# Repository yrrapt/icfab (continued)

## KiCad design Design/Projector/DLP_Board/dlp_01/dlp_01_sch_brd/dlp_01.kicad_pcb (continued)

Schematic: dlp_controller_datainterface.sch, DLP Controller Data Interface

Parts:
R48, R49, R50, R51: 7.87k; R_0603_1608Metric; part-num CRCW06037K87FKEA
U1, U2: DLPC3437; BGA-225_15x15_13.1x13.1mm; part-num DLPC3437CZEZ

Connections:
/application_connectors/DATEN_A: U2.P2 (DATAEN_CMD); also elsewhere on the board
/application_connectors/DATEN_B: U1.P2 (DATAEN_CMD); also elsewhere on the board
/application_connectors/HSYNC_A: U2.N5 (HSYNC_CS); also elsewhere on the board
/application_connectors/HSYNC_B: U1.N5 (HSYNC_CS); also elsewhere on the board
/application_connectors/IO_B34_LN4: U1.R9 (PDATA_22); also elsewhere on the board
/application_connectors/IO_B34_LN6: U1.R8 (PDATA_20); also elsewhere on the board
/application_connectors/IO_B34_LN8: U1.R7 (PDATA_18); also elsewhere on the board
/application_connectors/IO_B34_LN11: U1.R6 (PDATA_16); also elsewhere on the board
/application_connectors/IO_B34_LP4: U1.P10 (PDATA_23); also elsewhere on the board
/application_connectors/IO_B34_LP6: U1.P9 (PDATA_21); also elsewhere on the board
/application_connectors/IO_B34_LP8: U1.P8 (PDATA_19); also elsewhere on the board
/application_connectors/IO_B34_LP11: U1.P7 (PDATA_17); also elsewhere on the board
/application_connectors/IO_B35_LN2: U2.R9 (PDATA_22); also elsewhere on the board
/application_connectors/IO_B35_LN4: U2.R8 (PDATA_20); also elsewhere on the board
/application_connectors/IO_B35_LN6: U2.R7 (PDATA_18); also elsewhere on the board
/application_connectors/IO_B35_LN8: U2.R6 (PDATA_16); also elsewhere on the board
/application_connectors/IO_B35_LN10: U2.R5 (PDATA_14); also elsewhere on the board
/application_connectors/IO_B35_LN14: U2.R4 (PDATA_12); also elsewhere on the board
/application_connectors/IO_B35_LN16: U2.R3 (PDATA_10); also elsewhere on the board
/application_connectors/IO_B35_LN18: U2.R1 (PDATA_8); also elsewhere on the board
/application_connectors/IO_B35_LN20: U2.N2 (PDATA_6); also elsewhere on the board
/application_connectors/IO_B35_LN22: U2.M2 (PDATA_4); also elsewhere on the board
/application_connectors/IO_B35_LN23: U2.K1 (PDATA_1); also elsewhere on the board
/application_connectors/IO_B35_LN24: U2.L2 (PDATA_2); also elsewhere on the board
/application_connectors/IO_B35_LP2: U2.P10 (PDATA_23); also elsewhere on the board
/application_connectors/IO_B35_LP4: U2.P9 (PDATA_21); also elsewhere on the board
/application_connectors/IO_B35_LP6: U2.P8 (PDATA_19); also elsewhere on the board
/application_connectors/IO_B35_LP8: U2.P7 (PDATA_17); also elsewhere on the board
/application_connectors/IO_B35_LP10: U2.P6 (PDATA_15); also elsewhere on the board
/application_connectors/IO_B35_LP14: U2.P5 (PDATA_13); also elsewhere on the board
/application_connectors/IO_B35_LP16: U2.P4 (PDATA_11); also elsewhere on the board
/application_connectors/IO_B35_LP18: U2.R2 (PDATA_9); also elsewhere on the board
/application_connectors/IO_B35_LP20: U2.N1 (PDATA_7); also elsewhere on the board
/application_connectors/IO_B35_LP22: U2.M1 (PDATA_5); also elsewhere on the board
/application_connectors/IO_B35_LP23: U2.K2 (PDATA_0); also elsewhere on the board
/application_connectors/IO_B35_LP24: U2.L1 (PDATA_3); also elsewhere on the board
/application_connectors/LCD_DATA0: U1.K2 (PDATA_0); also elsewhere on the board
/application_connectors/LCD_DATA1: U1.K1 (PDATA_1); also elsewhere on the board
/application_connectors/LCD_DATA2: U1.L2 (PDATA_2); also elsewhere on the board
/application_connectors/LCD_DATA3: U1.L1 (PDATA_3); also elsewhere on the board
/application_connectors/LCD_DATA4: U1.M2 (PDATA_4); also elsewhere on the board
/application_connectors/LCD_DATA5: U1.M1 (PDATA_5); also elsewhere on the board
/application_connectors/LCD_DATA6: U1.N2 (PDATA_6); also elsewhere on the board
/application_connectors/LCD_DATA7: U1.N1 (PDATA_7); also elsewhere on the board
/application_connectors/LCD_DATA8: U1.R1 (PDATA_8); also elsewhere on the board
/application_connectors/LCD_DATA9: U1.R2 (PDATA_9); also elsewhere on the board
/application_connectors/LCD_DATA10: U1.R3 (PDATA_10); also elsewhere on the board
/application_connectors/LCD_DATA11: U1.P4 (PDATA_11); also elsewhere on the board
/application_connectors/LCD_DATA12: U1.R4 (PDATA_12); also elsewhere on the board
/application_connectors/LCD_DATA13: U1.P5 (PDATA_13); also elsewhere on the board
/application_connectors/LCD_DATA14: U1.R5 (PDATA_14); also elsewhere on the board
/application_connectors/LCD_DATA15: U1.P6 (PDATA_15); also elsewhere on the board
/application_connectors/PCLK_A: U2.P3 (PCLK); also elsewhere on the board
/application_connectors/PCLK_B: U1.P3 (PCLK); also elsewhere on the board
/application_connectors/PDM_CVS_TE_A: R51.2, U2.N4 (PDM_CVS_TE); also elsewhere on the board
/application_connectors/PDM_CVS_TE_B: R49.2, U1.N4 (PDM_CVS_TE); also elsewhere on the board
/application_connectors/VSYNC_A: U2.P1 (VSYNC_WE); also elsewhere on the board
/application_connectors/VSYNC_B: U1.P1 (VSYNC_WE); also elsewhere on the board
GND: R48.2, R49.1, R50.2, R51.1; also elsewhere on the board
unnamed: R48.1, U1.N6 (3DR)
unnamed: R50.1, U2.N6 (3DR)

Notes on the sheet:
Slave
Master

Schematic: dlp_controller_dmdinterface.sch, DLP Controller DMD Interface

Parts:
R52, R53: 43R; R_0603_1608Metric; part-num CRCW060343R0FKEA
U1, U2: DLPC3437; BGA-225_15x15_13.1x13.1mm; part-num DLPC3437CZEZ

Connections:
/dlp_controller/DMD_DEN_ARSTZ: U1.B1 (DMD_DEN_ARSTZ); also elsewhere on the board
/dlp_controller/DMD_LS_CLK: R52.2; also elsewhere on the board
/dlp_controller/DMD_LS_RDATA: U1.B2 (DMD_LS_RDATA); also elsewhere on the board
/dlp_controller/DMD_LS_WDATA: R53.2; also elsewhere on the board
/dlp_controller/mDMD_HS_CLK_N: U1.B7 (DMD_HS_CLK_N); also elsewhere on the board
/dlp_controller/mDMD_HS_CLK_P: U1.A7 (DMD_HS_CLK_P); also elsewhere on the board
/dlp_controller/mDMD_HS_WDATAA_N: U1.B11 (DMD_HS_WDATA_A_N); also elsewhere on the board
/dlp_controller/mDMD_HS_WDATAA_P: U1.A11 (DMD_HS_WDATA_A_P); also elsewhere on the board
/dlp_controller/mDMD_HS_WDATAB_N: U1.B10 (DMD_HS_WDATA_B_N); also elsewhere on the board
/dlp_controller/mDMD_HS_WDATAB_P: U1.A10 (DMD_HS_WDATA_B_P); also elsewhere on the board
/dlp_controller/mDMD_HS_WDATAC_N: U1.B9 (DMD_HS_WDATA_C_N); also elsewhere on the board
/dlp_controller/mDMD_HS_WDATAC_P: U1.A9 (DMD_HS_WDATA_C_P); also elsewhere on the board
/dlp_controller/mDMD_HS_WDATAD_N: U1.B8 (DMD_HS_WDATA_D_N); also elsewhere on the board
/dlp_controller/mDMD_HS_WDATAD_P: U1.A8 (DMD_HS_WDATA_D_P); also elsewhere on the board
/dlp_controller/mDMD_HS_WDATAE_N: U1.B6 (DMD_HS_WDATA_E_N); also elsewhere on the board
/dlp_controller/mDMD_HS_WDATAE_P: U1.A6 (DMD_HS_WDATA_E_P); also elsewhere on the board
/dlp_controller/mDMD_HS_WDATAF_N: U1.B5 (DMD_HS_WDATA_F_N); also elsewhere on the board
/dlp_controller/mDMD_HS_WDATAF_P: U1.A5 (DMD_HS_WDATA_F_P); also elsewhere on the board
/dlp_controller/mDMD_HS_WDATAG_N: U1.B4 (DMD_HS_WDATA_G_N); also elsewhere on the board
/dlp_controller/mDMD_HS_WDATAG_P: U1.A4 (DMD_HS_WDATA_G_P); also elsewhere on the board
/dlp_controller/mDMD_HS_WDATAH_N: U1.B3 (DMD_HS_WDATA_H_N); also elsewhere on the board
/dlp_controller/mDMD_HS_WDATAH_P: U1.A3 (DMD_HS_WDATA_H_P); also elsewhere on the board
/dlp_controller/sDMD_HS_CLK_N: U2.B7 (DMD_HS_CLK_N); also elsewhere on the board
/dlp_controller/sDMD_HS_CLK_P: U2.A7 (DMD_HS_CLK_P); also elsewhere on the board
/dlp_controller/sDMD_HS_WDATAA_N: U2.B11 (DMD_HS_WDATA_A_N); also elsewhere on the board
/dlp_controller/sDMD_HS_WDATAA_P: U2.A11 (DMD_HS_WDATA_A_P); also elsewhere on the board
/dlp_controller/sDMD_HS_WDATAB_N: U2.B10 (DMD_HS_WDATA_B_N); also elsewhere on the board
/dlp_controller/sDMD_HS_WDATAB_P: U2.A10 (DMD_HS_WDATA_B_P); also elsewhere on the board
/dlp_controller/sDMD_HS_WDATAC_N: U2.B9 (DMD_HS_WDATA_C_N); also elsewhere on the board
/dlp_controller/sDMD_HS_WDATAC_P: U2.A9 (DMD_HS_WDATA_C_P); also elsewhere on the board
/dlp_controller/sDMD_HS_WDATAD_N: U2.B8 (DMD_HS_WDATA_D_N); also elsewhere on the board
/dlp_controller/sDMD_HS_WDATAD_P: U2.A8 (DMD_HS_WDATA_D_P); also elsewhere on the board
/dlp_controller/sDMD_HS_WDATAE_N: U2.B6 (DMD_HS_WDATA_E_N); also elsewhere on the board
/dlp_controller/sDMD_HS_WDATAE_P: U2.A6 (DMD_HS_WDATA_E_P); also elsewhere on the board
/dlp_controller/sDMD_HS_WDATAF_N: U2.B5 (DMD_HS_WDATA_F_N); also elsewhere on the board
/dlp_controller/sDMD_HS_WDATAF_P: U2.A5 (DMD_HS_WDATA_F_P); also elsewhere on the board
/dlp_controller/sDMD_HS_WDATAG_N: U2.A4 (DMD_HS_WDATA_G_P); also elsewhere on the board
/dlp_controller/sDMD_HS_WDATAG_P: U2.B4 (DMD_HS_WDATA_G_N); also elsewhere on the board
/dlp_controller/sDMD_HS_WDATAH_N: U2.B3 (DMD_HS_WDATA_H_N); also elsewhere on the board
/dlp_controller/sDMD_HS_WDATAH_P: U2.A3 (DMD_HS_WDATA_H_P); also elsewhere on the board
/dlp_controller/sDMD_LS_RDATA: U2.B2 (DMD_LS_RDATA); also elsewhere on the board
unnamed: R52.1, U1.A1 (DMD_LS_CLK)
unnamed: R53.1, U1.A2 (DMD_LS_WDATA)

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
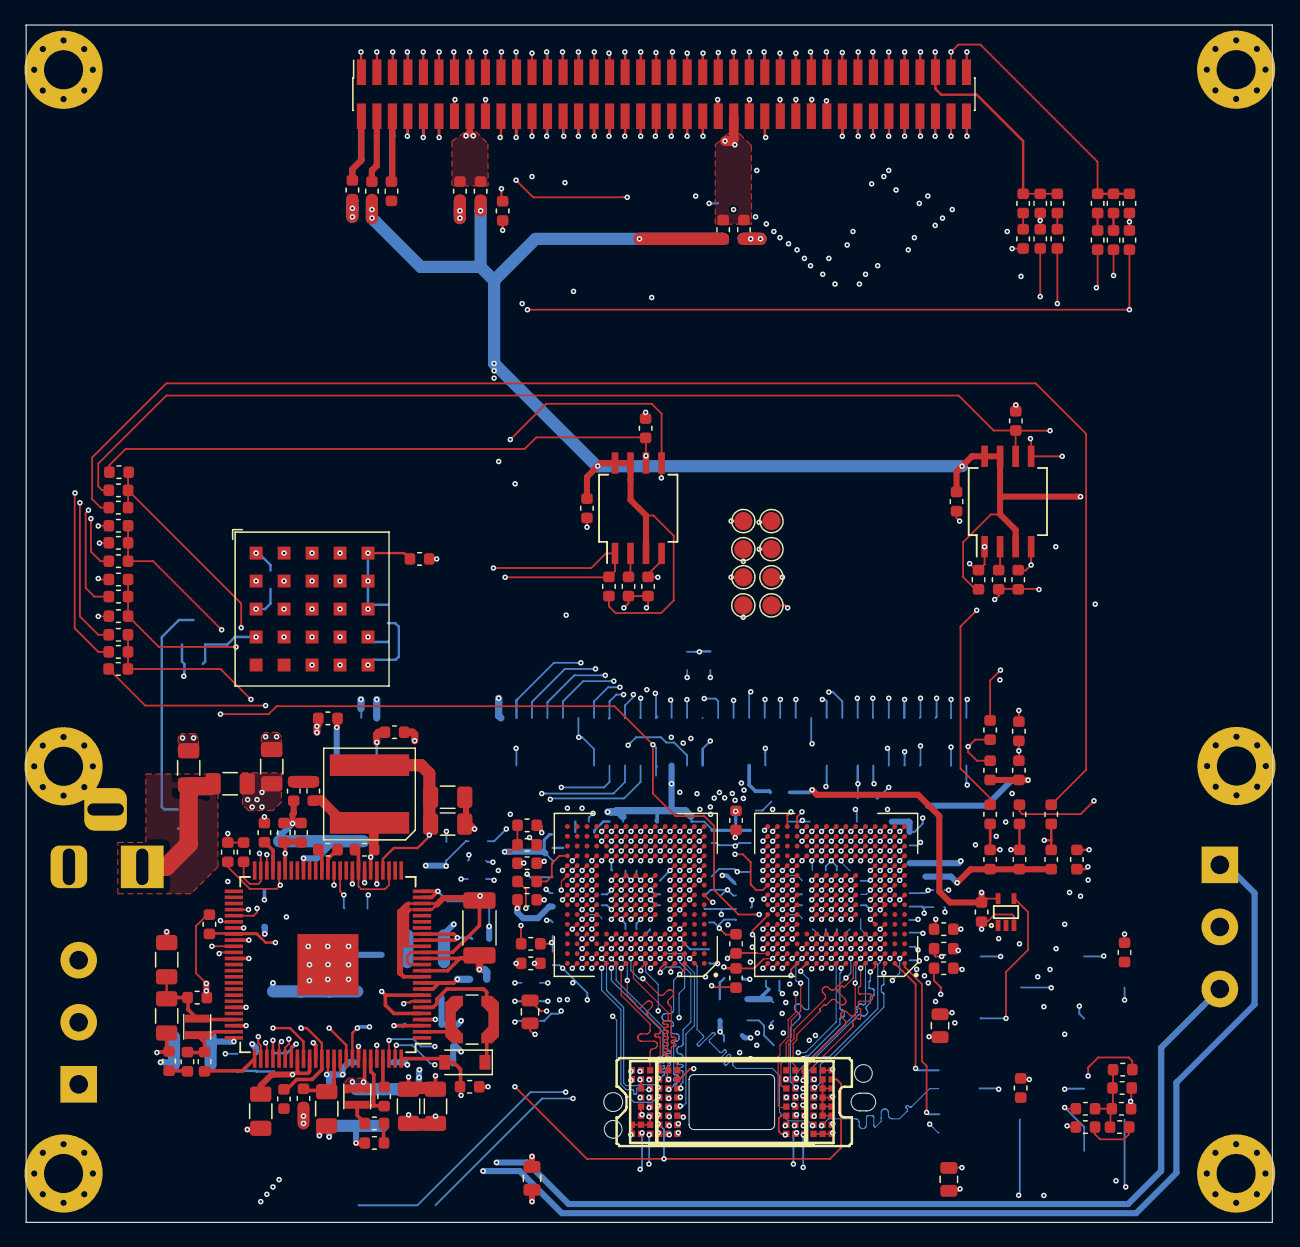
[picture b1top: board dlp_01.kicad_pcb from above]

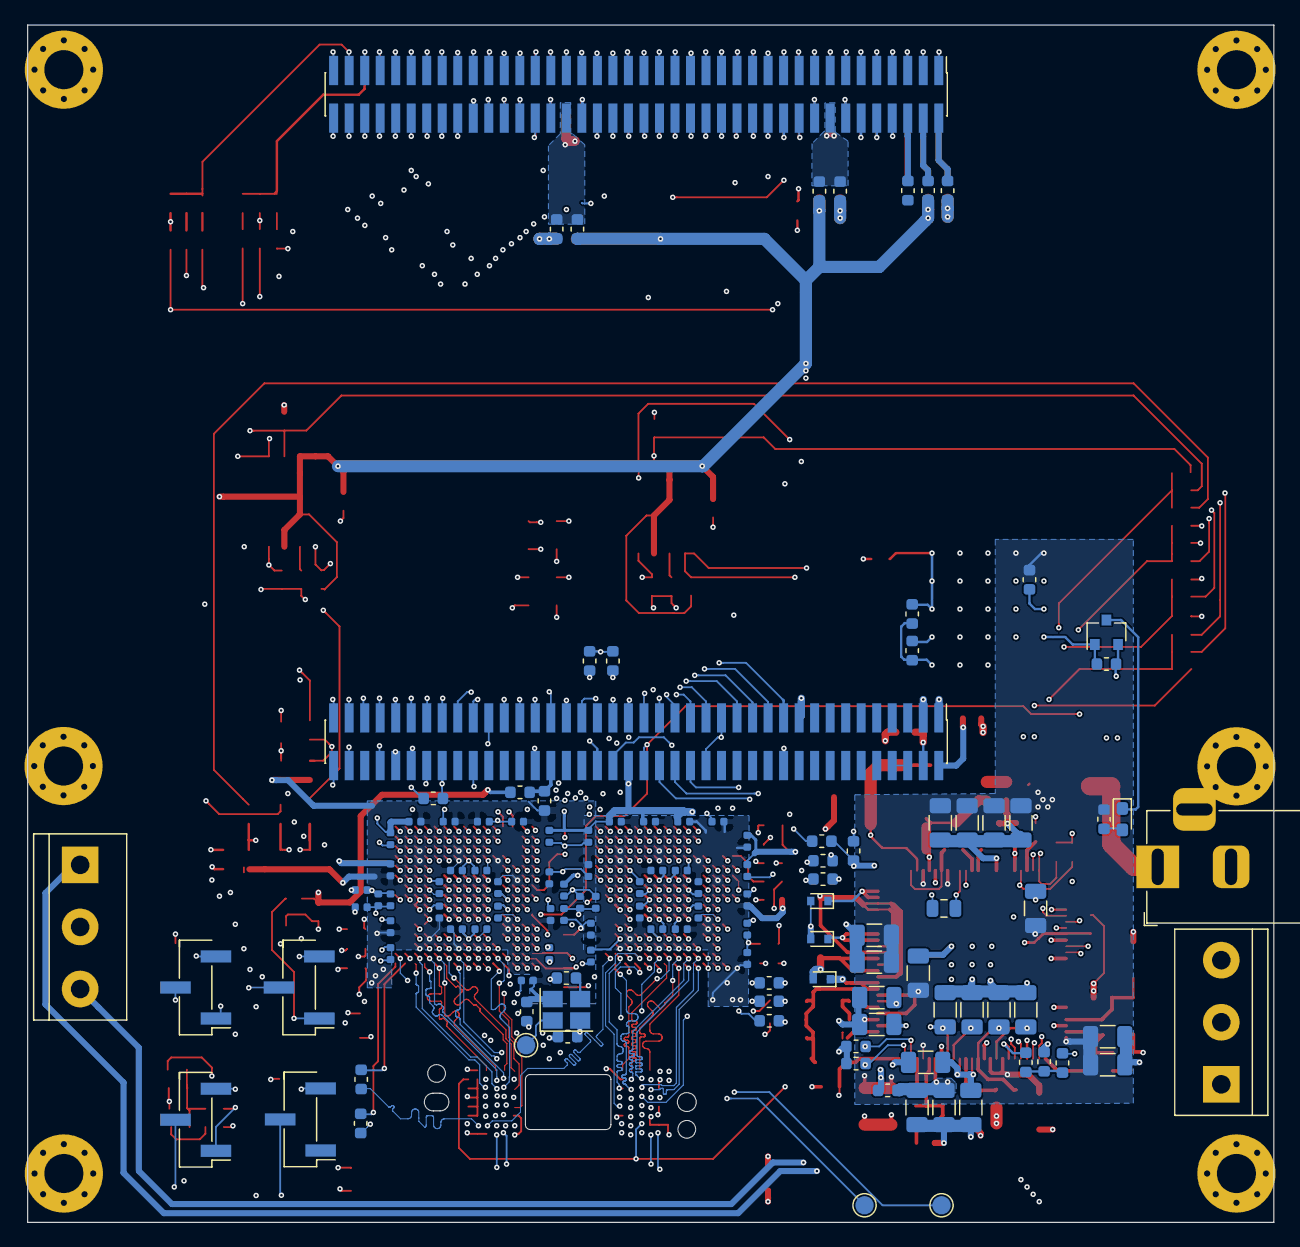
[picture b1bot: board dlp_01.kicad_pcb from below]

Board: 6 copper layers, 102.0 x 98.0 mm, 266 parts (124 on the bottom side), 295 nets.

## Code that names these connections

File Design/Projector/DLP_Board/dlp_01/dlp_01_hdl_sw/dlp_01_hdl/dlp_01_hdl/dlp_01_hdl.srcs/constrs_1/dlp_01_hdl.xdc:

set_property IOSTANDARD {LVCMOS33 [get_ports PDM_CVS_TE_B}]
set_property IOSTANDARD {LVCMOS33 [get_ports HSYNC_B}]
set_property IOSTANDARD {LVCMOS33 [get_ports VSYNC_B}]
set_property IOSTANDARD {LVCMOS33 [get_ports DATEN_B}]
set_property IOSTANDARD {LVCMOS33 [get_ports O3DR_B}]
set_property IOSTANDARD {LVCMOS33 [get_ports PDAT_B[0]}]
set_property IOSTANDARD {LVCMOS33 [get_ports PDAT_B[1]}]
set_property IOSTANDARD {LVCMOS33 [get_ports PDAT_B[2]}]
set_property IOSTANDARD {LVCMOS33 [get_ports PDAT_B[3]}]
set_property IOSTANDARD {LVCMOS33 [get_ports PDAT_B[4]}]
set_property IOSTANDARD {LVCMOS33 [get_ports PDAT_B[5]}]
set_property IOSTANDARD {LVCMOS33 [get_ports PDAT_B[6]}]
set_property IOSTANDARD {LVCMOS33 [get_ports PDAT_B[7]}]
set_property IOSTANDARD {LVCMOS33 [get_ports PDAT_B[8]}]
set_property IOSTANDARD {LVCMOS33 [get_ports PDAT_B[9]}]
set_property IOSTANDARD {LVCMOS33 [get_ports PDAT_B[10]}]
set_property IOSTANDARD {LVCMOS33 [get_ports PDAT_B[11]}]
set_property IOSTANDARD {LVCMOS33 [get_ports PDAT_B[12]}]
set_property IOSTANDARD {LVCMOS33 [get_ports PDAT_B[13]}]
set_property IOSTANDARD {LVCMOS33 [get_ports PDAT_B[14]}]
set_property IOSTANDARD {LVCMOS33 [get_ports PDAT_B[15]}]
set_property IOSTANDARD {LVCMOS33 [get_ports PDAT_B[16]}]
set_property IOSTANDARD {LVCMOS33 [get_ports PDAT_B[17]}]
set_property IOSTANDARD {LVCMOS33 [get_ports PDAT_B[18]}]
set_property IOSTANDARD {LVCMOS33 [get_ports PDAT_B[19]}]
set_property IOSTANDARD {LVCMOS33 [get_ports PDAT_B[20]}]
set_property IOSTANDARD {LVCMOS33 [get_ports PDAT_B[21]}]
set_property IOSTANDARD {LVCMOS33 [get_ports PDAT_B[22]}]
set_property IOSTANDARD {LVCMOS33 [get_ports PDAT_B[23]}]
set_property IOSTANDARD {LVCMOS33 [get_ports FPGA_RDY}]
set_property IOSTANDARD {LVCMOS33 [get_ports ACT_SYNC}]
set_property IOSTANDARD {LVCMOS33 [get_ports SUB_FRAME}]
set_property IOSTANDARD {LVCMOS33 [get_ports PROJ_ON}]
set_property IOSTANDARD {LVCMOS33 [get_ports sHOST_IRQ}]
set_property IOSTANDARD {LVCMOS33 [get_ports mHOST_IRQ}]
set_property IOSTANDARD {LVCMOS33 [get_ports PCLK_B}]
set_property IOSTANDARD {LVCMOS33 [get_ports PDM_CVS_TE_A}]
set_property IOSTANDARD {LVCMOS33 [get_ports HSYNC_A}]
set_property IOSTANDARD {LVCMOS33 [get_ports VSYNC_A}]
set_property IOSTANDARD {LVCMOS33 [get_ports DATEN_A}]
set_property IOSTANDARD {LVCMOS33 [get_ports O3DR_A}]
set_property IOSTANDARD {LVCMOS33 [get_ports PDAT_A[0]}]
set_property IOSTANDARD {LVCMOS33 [get_ports PDAT_A[1]}]
set_property IOSTANDARD {LVCMOS33 [get_ports PDAT_A[2]}]
set_property IOSTANDARD {LVCMOS33 [get_ports PDAT_A[3]}]
set_property IOSTANDARD {LVCMOS33 [get_ports PDAT_A[4]}]
set_property IOSTANDARD {LVCMOS33 [get_ports PDAT_A[5]}]
set_property IOSTANDARD {LVCMOS33 [get_ports PDAT_A[6]}]
set_property IOSTANDARD {LVCMOS33 [get_ports PDAT_A[7]}]
set_property IOSTANDARD {LVCMOS33 [get_ports PDAT_A[8]}]
set_property IOSTANDARD {LVCMOS33 [get_ports PDAT_A[9]}]
set_property IOSTANDARD {LVCMOS33 [get_ports PDAT_A[10]}]
set_property IOSTANDARD {LVCMOS33 [get_ports PDAT_A[11]}]
set_property IOSTANDARD {LVCMOS33 [get_ports PDAT_A[12]}]
set_property IOSTANDARD {LVCMOS33 [get_ports PDAT_A[13]}]
set_property IOSTANDARD {LVCMOS33 [get_ports PDAT_A[14]}]
set_property IOSTANDARD {LVCMOS33 [get_ports PDAT_A[15]}]
set_property IOSTANDARD {LVCMOS33 [get_ports PDAT_A[16]}]
set_property IOSTANDARD {LVCMOS33 [get_ports PDAT_A[17]}]
set_property IOSTANDARD {LVCMOS33 [get_ports PDAT_A[18]}]
set_property IOSTANDARD {LVCMOS33 [get_ports PDAT_A[19]}]
set_property IOSTANDARD {LVCMOS33 [get_ports PDAT_A[20]}]
set_property IOSTANDARD {LVCMOS33 [get_ports PDAT_A[21]}]
set_property IOSTANDARD {LVCMOS33 [get_ports PDAT_A[22]}]
set_property IOSTANDARD {LVCMOS33 [get_ports PDAT_A[23]}]
set_property IOSTANDARD {LVCMOS33 [get_ports SCL}]
set_property IOSTANDARD {LVCMOS33 [get_ports SDA}]


set_property PACKAGE_PIN H17 [get_ports {PDM_CVS_TE_B}]
set_property PACKAGE_PIN F19 [get_ports {HSYNC_B}]
set_property PACKAGE_PIN F20 [get_ports {VSYNC_B}]
set_property PACKAGE_PIN T12 [get_ports {DATEN_B}]
set_property PACKAGE_PIN U12 [get_ports {O3DR_B}]
set_property PACKAGE_PIN T16 [get_ports {PDAT_B[0]}]
set_property PACKAGE_PIN U17 [get_ports {PDAT_B[1]}]
set_property PACKAGE_PIN V15 [get_ports {PDAT_B[2]}]
set_property PACKAGE_PIN W15 [get_ports {PDAT_B[3]}]
set_property PACKAGE_PIN U18 [get_ports {PDAT_B[4]}]
set_property PACKAGE_PIN U19 [get_ports {PDAT_B[5]}]
set_property PACKAGE_PIN N18 [get_ports {PDAT_B[6]}]
set_property PACKAGE_PIN P19 [get_ports {PDAT_B[7]}]
set_property PACKAGE_PIN N20 [get_ports {PDAT_B[8]}]
set_property PACKAGE_PIN P20 [get_ports {PDAT_B[9]}]
set_property PACKAGE_PIN T20 [get_ports {PDAT_B[10]}]
set_property PACKAGE_PIN U20 [get_ports {PDAT_B[11]}]
set_property PACKAGE_PIN V20 [get_ports {PDAT_B[12]}]
set_property PACKAGE_PIN W20 [get_ports {PDAT_B[13]}]
set_property PACKAGE_PIN Y18 [get_ports {PDAT_B[14]}]
set_property PACKAGE_PIN Y19 [get_ports {PDAT_B[15]}]
set_property PACKAGE_PIN U15 [get_ports {PDAT_B[16]}]
set_property PACKAGE_PIN U14 [get_ports {PDAT_B[17]}]
set_property PACKAGE_PIN Y14 [get_ports {PDAT_B[18]}]
set_property PACKAGE_PIN W14 [get_ports {PDAT_B[19]}]
set_property PACKAGE_PIN F17 [get_ports {PDAT_B[20]}]
set_property PACKAGE_PIN F16 [get_ports {PDAT_B[21]}]
set_property PACKAGE_PIN D20 [get_ports {PDAT_B[22]}]
set_property PACKAGE_PIN D19 [get_ports {PDAT_B[23]}]
set_property PACKAGE_PIN E18 [get_ports {FPGA_RDY}]
set_property PACKAGE_PIN E19 [get_ports {ACT_SYNC}]
set_property PACKAGE_PIN M19 [get_ports {SUB_FRAME}]
set_property PACKAGE_PIN M20 [get_ports {PROJ_ON}]
set_property PACKAGE_PIN L19 [get_ports {sHOST_IRQ}]
set_property PACKAGE_PIN L20 [get_ports {mHOST_IRQ}]
set_property PACKAGE_PIN H16 [get_ports {PCLK_B}]
set_property PACKAGE_PIN H17 [get_ports {PDM_CVS_TE_A}]
set_property PACKAGE_PIN H15 [get_ports {HSYNC_A}]
set_property PACKAGE_PIN G15 [get_ports {VSYNC_A}]
set_property PACKAGE_PIN N15 [get_ports {DATEN_A}]
set_property PACKAGE_PIN N16 [get_ports {O3DR_A}]
set_property PACKAGE_PIN M15 [get_ports {PDAT_A[0]}]
set_property PACKAGE_PIN M14 [get_ports {PDAT_A[1]}]
set_property PACKAGE_PIN J16 [get_ports {PDAT_A[2]}]
set_property PACKAGE_PIN K16 [get_ports {PDAT_A[3]}]
set_property PACKAGE_PIN L15 [get_ports {PDAT_A[4]}]
set_property PACKAGE_PIN L14 [get_ports {PDAT_A[5]}]
set_property PACKAGE_PIN J14 [get_ports {PDAT_A[6]}]
set_property PACKAGE_PIN K14 [get_ports {PDAT_A[7]}]
set_property PACKAGE_PIN G20 [get_ports {PDAT_A[8]}]
set_property PACKAGE_PIN G19 [get_ports {PDAT_A[9]}]
set_property PACKAGE_PIN G18 [get_ports {PDAT_A[10]}]
set_property PACKAGE_PIN G17 [get_ports {PDAT_A[11]}]
set_property PACKAGE_PIN H18 [get_ports {PDAT_A[12]}]
set_property PACKAGE_PIN J18 [get_ports {PDAT_A[13]}]
set_property PACKAGE_PIN J19 [get_ports {PDAT_A[14]}]
set_property PACKAGE_PIN K19 [get_ports {PDAT_A[15]}]
set_property PACKAGE_PIN M18 [get_ports {PDAT_A[16]}]
set_property PACKAGE_PIN M17 [get_ports {PDAT_A[17]}]
set_property PACKAGE_PIN F17 [get_ports {PDAT_A[18]}]
set_property PACKAGE_PIN F16 [get_ports {PDAT_A[19]}]
set_property PACKAGE_PIN D20 [get_ports {PDAT_A[20]}]
set_property PACKAGE_PIN D19 [get_ports {PDAT_A[21]}]
set_property PACKAGE_PIN A20 [get_ports {PDAT_A[22]}]
set_property PACKAGE_PIN B19 [get_ports {PDAT_A[23]}]
set_property PACKAGE_PIN C20 [get_ports {SCL}]
set_property PACKAGE_PIN B20 [get_ports {SDA}]


set_property CFGBVS VCCO [current_design]
set_property CONFIG_VOLTAGE 3.3 [current_design]

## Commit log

2019-06-09 Added initial KiCad libraries for DLP ICs
2019-06-09 Added DLP3310 STEP model
2019-06-09 Added the DLP controller and power managment IC libraries
2019-06-10 Added more KiCad symbols/footprints
2019-06-10 Added initial DLP board schematics
2019-06-10 Moved ESDA18-1K library from design files to libraries
2019-06-13 Updated schematic with changes pulling together top level design
2019-06-13 Started initial HDL FPGA
2019-06-20 Updated incorrect DLP3310 symbol
2019-06-25 Modified the DLP3310 symbol to allow for idiosyntric schematic connection
2019-06-25 Ongoing updates the schematics
2019-06-30 More updates in the DLP board
2019-07-06 Added interposer 3D model
2019-07-13 Added new libraries downloaded from the internet
2019-07-14 Initial placement of power converters, BGA fanout and Z-turn board outline imported
2019-07-14 Added output of front mechanical section of DLP mount
2019-07-15 Added DXF version of the DLP front mechanical piece
2019-07-16 Added good DXF output DLP front assembly along with STEP file
2019-07-20 Initial component placement on PCB
2019-08-07 Added the DLP interposer step model
2019-09-09 Updated gitignore files
2019-09-09 Initial compilation of SDK project template
2019-09-09 Initial compilation of Vivado rough image output project
2019-09-09 Schematic and PCB complete ready for review
2019-09-09 Add pinout spreadsheet
2019-09-09 Delet old project files
2019-09-09 Remove Vivado run files from tracking
2019-09-10 Added step model of combined DLP3310 and interposer
2019-09-11 Final PCB tweaks and 3D model export
2019-09-14 Added missing 3D models to PCB
2019-09-14 Added newest STEP model and removed older WRL and STEP models
2020-01-26 Updated DLP board design
2021-05-01 Dump of uncommitted changes
2021-05-02 Added some documentation
2021-05-02 Add BOM
2021-05-02 Fix links
